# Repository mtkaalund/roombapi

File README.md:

# roombapi
Roomba PI, for controlling my ROOBA with a Raspberry PI Zero 2

Remember to add user to ```dialout```.

```sudo adduser ${USER} dialout```

## Create a python vent
First clone the project then in the project folder use the following command
```python3 -m vent env```

Then activate the enviroment
```source env/bin/activate```

Now we can install the requirements for the project
```pip install -r requirements.txt```

To deactivate the enviroment
```deactivate```

## Projects used in this project
[py-gpsd2](https://github.com/hatsunearu/py-gpsd2)
[RPLCD](https://pypi.org/project/RPLCD/)

## Other resources
[medium.com how to set up a RPI4 with LCD](https://medium.com/@thedyslexiccoder/how-to-set-up-a-raspberry-pi-4-with-lcd-display-using-i2c-backpack-189a0760ae15)
[RPLCD RTD.io](https://rplcd.readthedocs.io/en/stable/getting_started.html)
[GPSD austinsnerdythings.com](https://austinsnerdythings.com/2021/04/19/microsecond-accurate-ntp-with-a-raspberry-pi-and-pps-gps/)
[RPI GPS satsignal](https://www.satsignal.eu/ntp/Raspberry-Pi-quickstart.html)

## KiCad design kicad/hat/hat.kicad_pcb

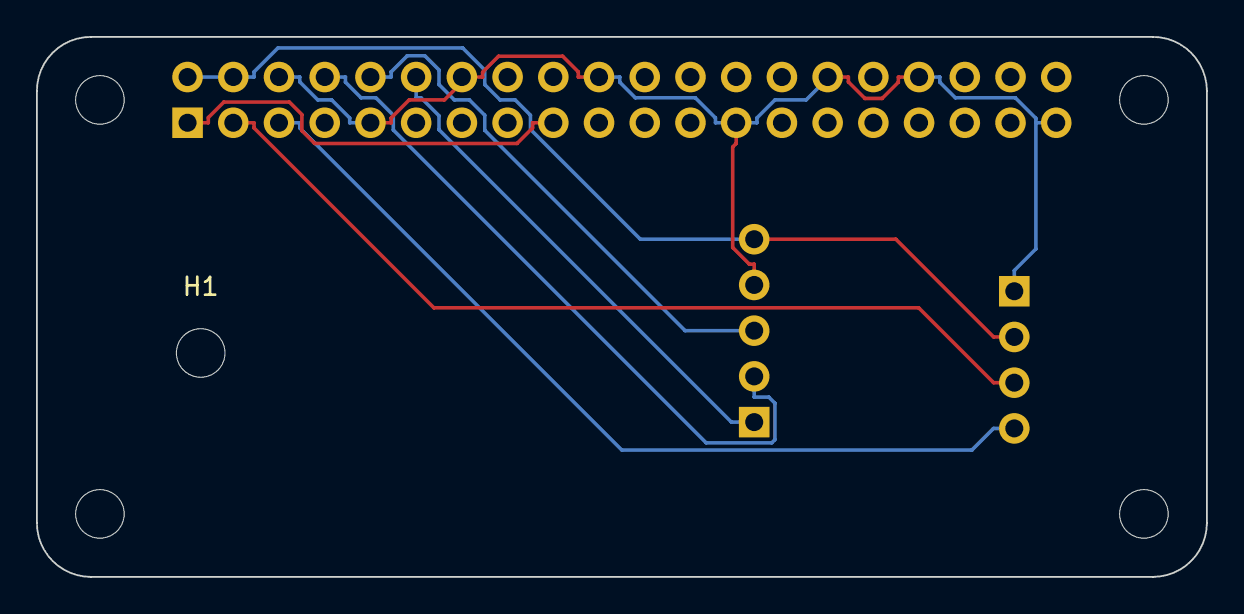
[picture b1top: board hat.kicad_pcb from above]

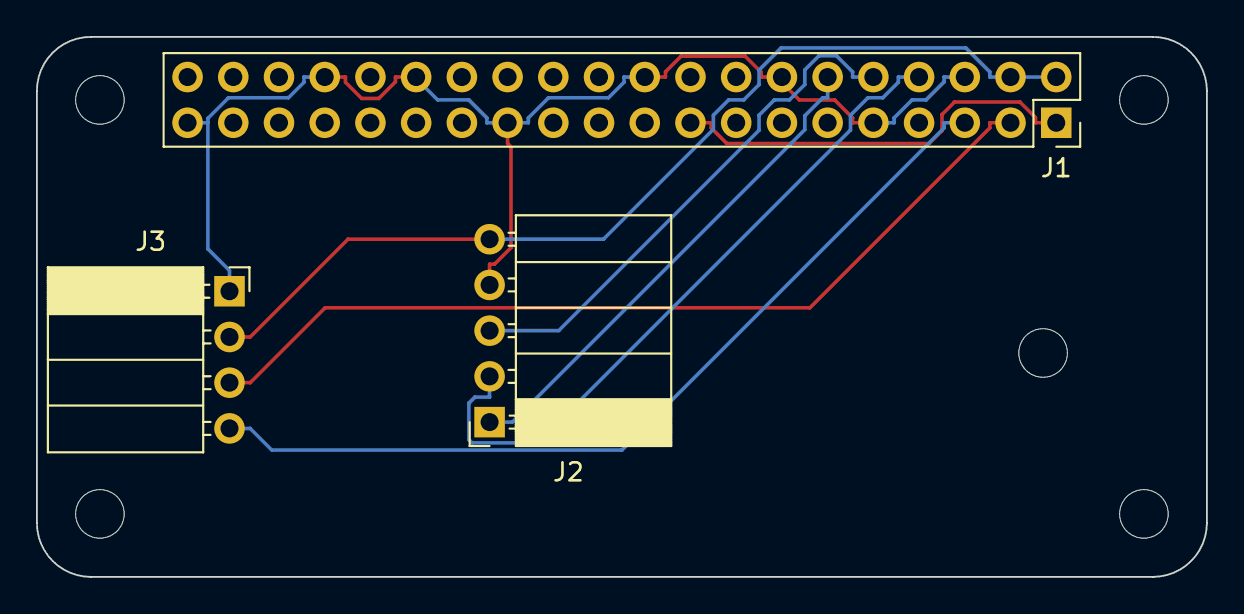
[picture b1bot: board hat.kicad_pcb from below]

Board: 2 copper layers, 65.0 x 30.0 mm, 8 parts (3 on the bottom side), 8 nets.

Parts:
H1: MountingHole; MountingHole_2.7mm
J1: GPIO; PinSocket_2x20_P2.54mm_Vertical
J2: GPS Connector; PinSocket_1x05_P2.54mm_Horizontal
J3: I2C; PinSocket_1x04_P2.54mm_Horizontal
MH1, MH2, MH3, MH4: MountingHole_2.7mm_M2.5

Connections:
+3V3: J1.1, J1.17
+5V: J1.2, J1.4, J2.5, J3.2
/GPIO2/SDA1: J1.3, J3.3
/GPIO3/SCL1: J1.5, J3.4
/GPIO14/TXD0: J1.8, J2.2
/GPIO15/RXD0: J1.10, J2.3
/GPIO18/PCM.CLK: J1.12, J2.1
GND: J1.6, J1.9, J1.14, J1.20, J1.25, J1.30, J1.34, J1.39, J2.4, J3.1

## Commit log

2024-09-16 Create requirements.txt
    python packages used in this project
2024-09-16 Update README.md
    with some instructions
2024-09-16 added .gitignore
2024-09-16 added a example for usafe on gpsd
2024-09-16 fixed typo in gps example
2024-09-16 added exception handling
2024-09-16 Moved alittle around
2024-09-16 Moved device information out
2024-09-16 some more test code gpsd2
2024-09-17 Example lcd display script
2024-09-17 Updated requirements.txt
2024-09-17 fixed type in lcd_display
2024-09-17 updated lcd_display with the correct cols and rows
2024-09-17 just soom display test
2024-09-17 added some resources to readme
2024-09-17 removed some time functions
2024-09-18 Begun work on a melting with lcd and gps
2024-09-18 changed double qoute to single
2024-09-18 added a time.sleep
2024-09-18 adding scapy and pandas
2024-09-18 wifi read network
2024-09-18 copy the code
2024-09-18 remove the change_channel
2024-09-18 wifi scanner
2024-09-18 parentecs
2024-09-19 Just some begun some work on a hat
2024-09-19 gpsd example c++
2024-09-21 Makefile for cpp
2024-09-21 Now the make file should work
2024-09-21 added array header to cpp
2024-09-21 added some spaces and time format to UNIX
2024-09-21 change timeformat to UTC
2024-09-21 Changed text
2024-09-22 Adding skyview
2024-09-22 adding dop meaning
2024-09-22 adding some more info on skyview
2024-09-22 added objs dir
2024-09-22 added some int
2024-09-22 update gitignore
2024-09-22 small updates to gpsd-example
2024-09-22 removed bbinary from repo
2024-09-22 adding sat gps
2024-09-22 added some more text
2024-09-24 finished with some example code for i2c
2024-09-24 added comment on where example code is from
2024-09-24 added i2c-test to Makefile
2024-09-24 added i2c-test to .gitignore
2024-09-24 tried something
2024-09-24 added strerror(err) to error messages
2024-09-24 create a i2c header for rpi
2024-09-24 added a deconstructor to i2c class
2024-09-24 using the class
2024-09-24 tried to set backlight
2024-09-24 reworked receive
2024-09-24 added some lcd defines, and removed old test code
2024-09-24 remove address from receive
2024-09-25 adding some defines
2024-09-25 added asm
2024-09-27 trying to make a lambda function for sending values to lcd
2024-09-27 add rs
2024-09-27 point to i2c
2024-09-27 added clear display
2024-09-27 adding some program output
2024-09-27 lambda added to reference
2024-09-27 removed adding device to lambda function
2024-09-27 added lcd_enable
2024-09-28 adding char, init to lcd
2024-09-28 now sends a msg
2024-09-28 now with string
2024-09-28 added returnhome
2024-09-29 added vscode settings
2024-09-29 begun work on a lcd class
2024-09-29 added default bus id to 0x27
